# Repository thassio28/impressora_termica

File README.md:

# impressora_termica
Impressora térmica  com atmega328p e cabeça térmica LTP02-245.

Para fazer uma impressão deve ser enviado o texto por meio da porta serial com o comando CR (13) ao final da frase, ao apertar o botão o texto é impresso e é retornado pela serial o texto recebido.

Tensão comunicação 3,3V
BAUD = 9600
Tensão máxima da cabeça térmica (VP) 8V.
Clock interno 8 Mhz

Código e esquema ainda em fase de desenvolvimento.

Versão 1

Video impresão de texto: https://youtube.com/shorts/1QFV2fXhjIA?feature=share

Atualização futura, impressão de imagem: https://youtube.com/shorts/7ARQ239Vu7w?feature=share

Versão 2
Atualização futura 2, talvez display OLED.

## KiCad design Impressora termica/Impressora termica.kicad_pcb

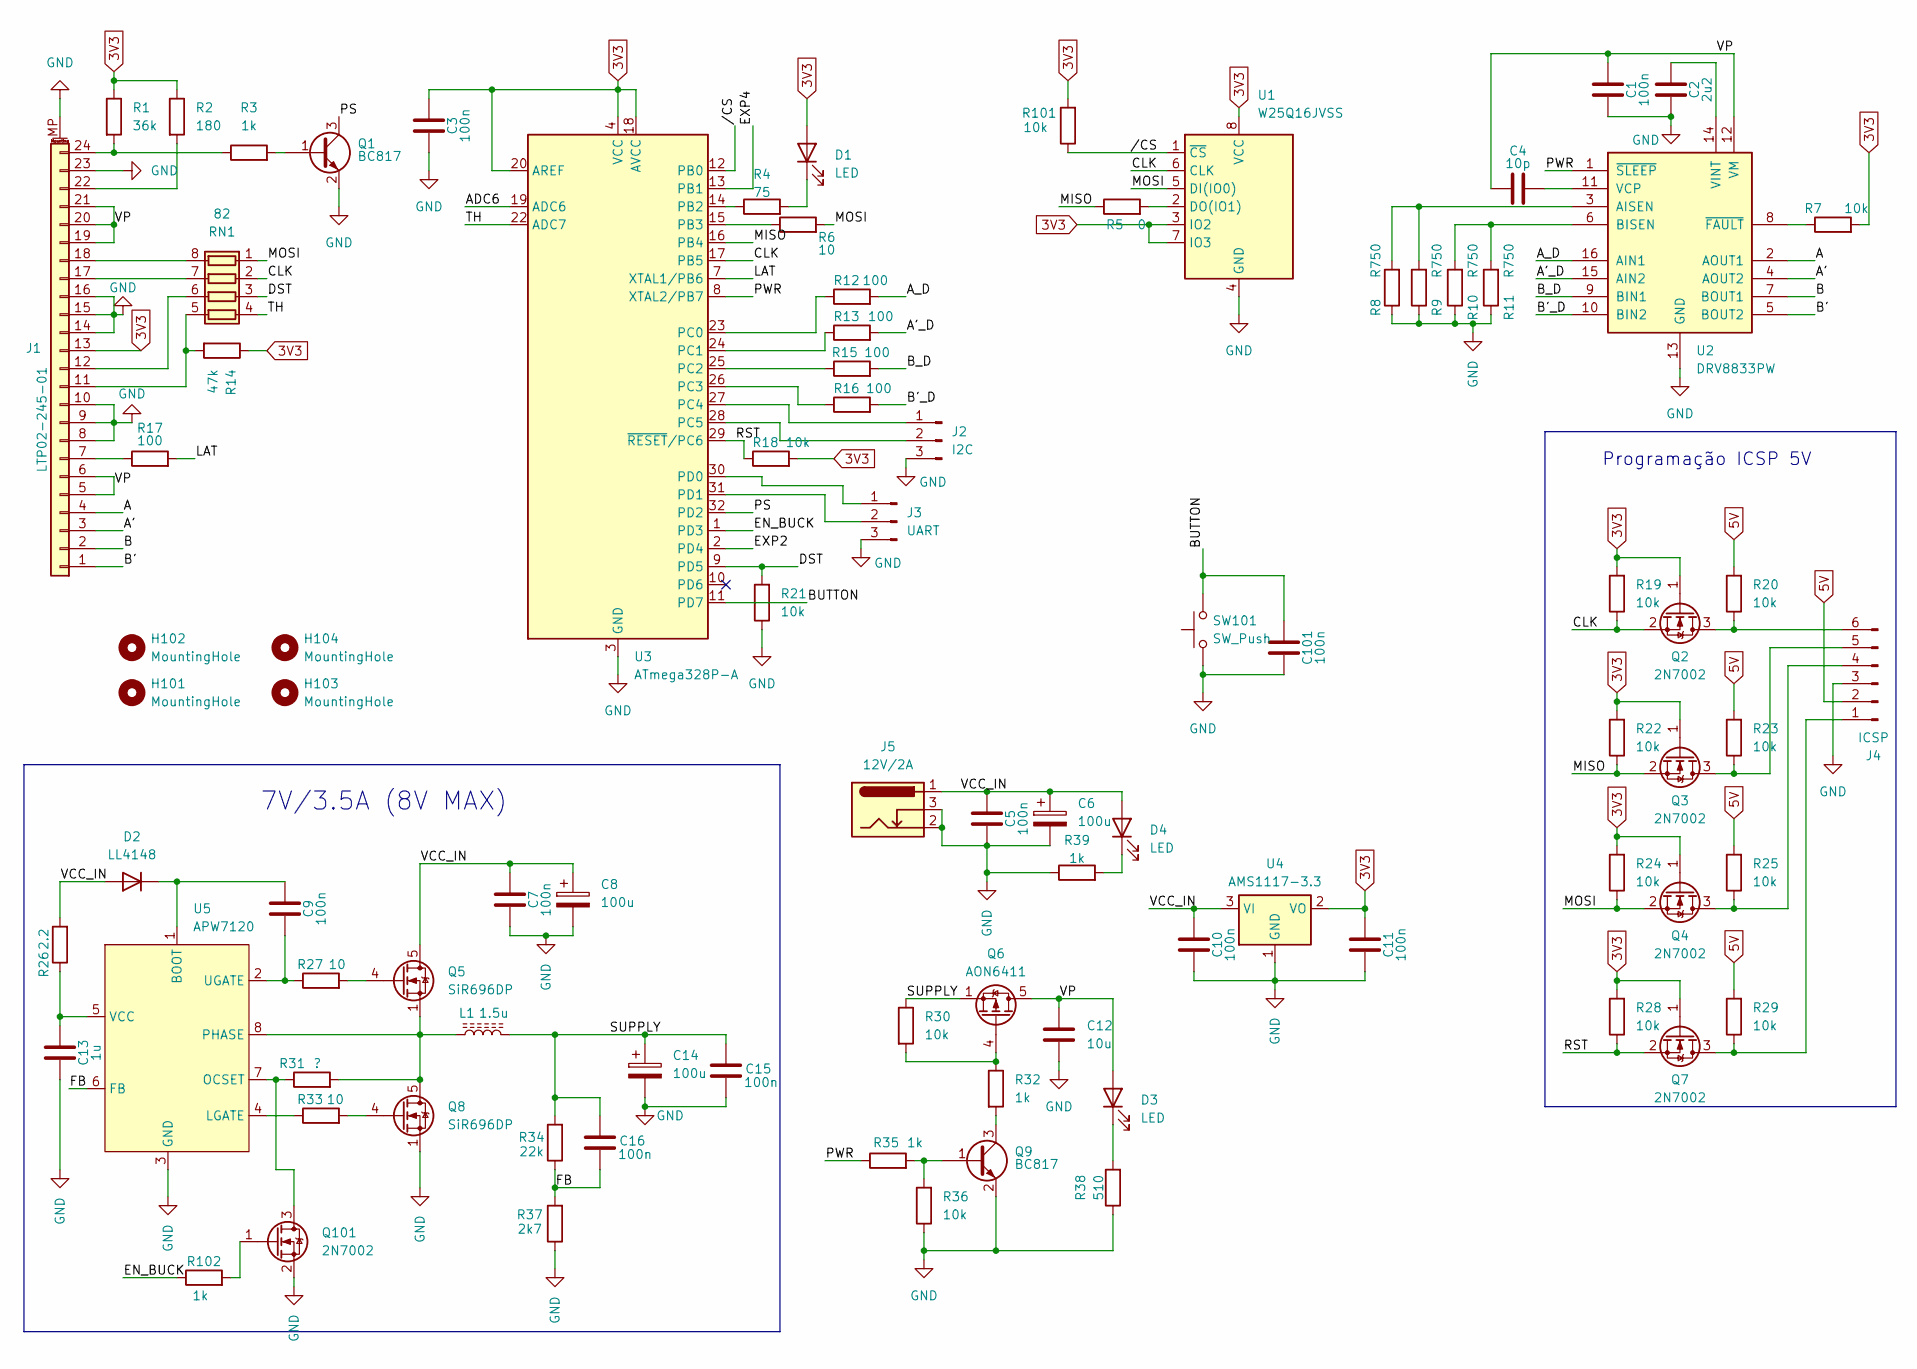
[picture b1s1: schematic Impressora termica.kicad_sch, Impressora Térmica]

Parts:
C1, C3, C5, C7, C9, C10, C11, C15, C16, C101: 100n; C_0805_2012Metric
C2: 2u2; C_0805_2012Metric
C4: 10p; C_0805_2012Metric
C6: 100u; CP_Elec_6.3x4.5
C8, C14: 100u; CP_Elec_5x4.5
C12: 10u; C_0805_2012Metric
C13: 1u; C_0805_2012Metric
D1, D3, D4: LED; LED_0805_2012Metric
D2: LL4148; D_MiniMELF
H101, H102, H103, H104: MountingHole; MountingHole_3.2mm_M3_DIN965
J1: LTP02-245-01; Hirose_FH12-24S-0.5SH_1x24-1MP_P0.50mm_Horizontal
J2: I2C; PinHeader_1x03_P2.54mm_Vertical
J3: UART; PinHeader_1x03_P2.54mm_Vertical
J4: ICSP; PinHeader_1x06_P2.54mm_Vertical
J5: 12V/2A; BarrelJack_GCT_DCJ200-10-A_Horizontal
L1: 1.5u; L_APV_ANR8040
Q1, Q9: BC817; SOT-23
Q2, Q3, Q4, Q7, Q101: 2N7002; SOT-23
Q5, Q8: SiR696DP; DFN8_3x3_EP_AOS
Q6: AON6411; DFN8_3x3_EP_AOS
R1: 36k; R_0603_1608Metric
R2: 180; R_0603_1608Metric
R3, R35: 1k; R_0805_2012Metric
R4: 75; R_0603_1608Metric
R5: 0; R_0603_1608Metric
R6: 10; R_0805_2012Metric
R7: 10k; R_1206_3216Metric
R8, R9, R10, R11: R750; R_0805_2012Metric
R12, R13, R15, R16: 100; R_0805_2012Metric
R14: 47k; R_0805_2012Metric
R17: 100; R_0603_1608Metric
R18: 10k; R_0805_2012Metric
R19, R20, R21, R22, R23, R24, R25, R28, R29, R30, R36, R101: 10k; R_0603_1608Metric
R26: 2.2; R_0805_2012Metric
R27, R33: 10; R_0603_1608Metric
R31: ?; R_0805_2012Metric
R32, R39, R102: 1k; R_0603_1608Metric
R34: 22k; R_0603_1608Metric
R37: 2k7; R_0603_1608Metric
R38: 510; R_0603_1608Metric
RN1: 82; R_Array_Convex_4x0603
SW101: SW_Push; SW_SPST_CK_RS282G05A3
U1: W25Q16JVSS; SOIC-8_5.23x5.23mm_P1.27mm
U2: DRV8833PW; TSSOP-16_4.4x5mm_P0.65mm
U3: ATmega328P-A; TQFP-32_7x7mm_P0.8mm
U4: AMS1117-3.3; SOT-223-3_TabPin2
U5: APW7120; SOP-8_5.28x5.23mm_P1.27mm

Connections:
3V3: C3.2, C11.2, D1.2 (A), J1.13, Q2.1 (G), Q3.1 (G), Q4.1 (G), Q7.1 (G), R1.1, R2.1, R7.2, R14.1, R18.2, R19.2, R22.2, R24.2, R28.2, R101.2, U1.3 (IO2), U1.7 (IO3), U1.8 (VCC), U3.4 (VCC), U3.6 (VCC), U3.18 (AVCC), U3.20 (AREF), U4.2 (VO)
5V: J4.2, R20.2, R23.2, R25.2, R29.2
/A: J1.4, U2.2 (AOUT1)
/A': J1.3, U2.4 (AOUT2)
/A'_D: R13.2, U2.15 (AIN2)
/ADC6: U3.19 (ADC6)
/A_D: R12.2, U2.16 (AIN1)
/B: J1.2, U2.7 (BOUT1)
/B': J1.1, U2.5 (BOUT2)
/B'_D: R16.2, U2.10 (BIN2)
/BUTTON: C101.2, SW101.2, U3.11 (PD7)
/B_D: R15.2, U2.9 (BIN1)
/CLK: Q2.2 (S), R19.1, RN1.2 (R2.1), U1.6 (CLK), U3.17 (PB5)
/DST: R21.2, RN1.3 (R3.1), U3.9 (PD5)
/EN_BUCK: R102.1, U3.1 (PD3)
/EXP2: U3.2 (PD4)
/EXP4: U3.13 (PB1)
/FB: C16.1, R34.1, R37.2, U5.6 (FB)
/LAT: R17.2, U3.7 (XTAL1/PB6)
/MISO: Q3.2 (S), R5.1, R22.1, U3.16 (PB4)
/MOSI: Q4.2 (S), R6.2, R24.1, RN1.1 (R1.1), U1.5 (DI(IO0))
/PS: Q1.3 (C), U3.32 (PD2)
/PWR: R35.1, U2.1 (~SLEEP), U3.8 (XTAL2/PB7)
/RST: Q7.2 (S), R18.1, R28.1, U3.29 (~RESET/PC6)
/SUPPLY: C14.1, C15.2, C16.2, L1.2, Q6.1 (S), Q6.2 (S), Q6.3 (S), R30.1, R34.2
/TH: RN1.4 (R4.1), U3.22 (ADC7)
/VCC_IN: C5.2, C6.1, C7.2, C8.1, C10.2, D2.2 (A), D4.2 (A), J5.1, Q5.5 (D), R26.2, U4.3 (VI)
/VP: C1.2, C4.1, C12.1, D3.2 (A), J1.5, J1.6, J1.19, J1.20, J1.21, Q6.5 (D), U2.12 (VM)
//CS: R101.1, U1.1 (~CS), U3.12 (PB0)
GND: C1.1, C2.1, C3.1, C5.1, C6.2, C7.1, C8.2, C10.1, C11.1, C12.2, C13.1, C14.2, C15.1, C101.1, J1.8, J1.9, J1.10, J1.14, J1.15, J1.16, J1.23, J1.MP (MountPin), J2.3, J3.3, J4.3, J5.2, J5.3, Q1.2 (E), Q8.1 (S), Q8.2 (S), Q8.3 (S), Q9.2 (E), Q101.2 (S), R8.1, R9.1, R10.1, R11.1, R21.1, R36.1, R37.1, R38.1, R39.1, SW101.1, U1.4 (GND), U2.13 (GND), U3.3 (GND), U3.5 (GND), U3.21 (GND), U4.1 (GND), U5.3 (GND)
unnamed: D1.1 (K), R4.2
unnamed: C9.2, D2.1 (K), U5.1 (BOOT)
unnamed: D3.1 (K), R38.2
unnamed: D4.1 (K), R39.2
unnamed: J1.7, R17.1
unnamed: J1.11, R14.2, RN1.5 (R4.2)
unnamed: J1.12, RN1.6 (R3.2)
unnamed: J1.17, RN1.7 (R2.2)
unnamed: J1.18, RN1.8 (R1.2)
unnamed: J1.22, R2.2
unnamed: J1.24, R1.2, R3.1
unnamed: J2.1, U3.27 (PC4)
unnamed: J2.2, U3.28 (PC5)
unnamed: J3.1, U3.30 (PD0)
unnamed: J3.2, U3.31 (PD1)
unnamed: J4.1, Q7.3 (D), R29.1
unnamed: J4.4, Q4.3 (D), R25.1
unnamed: J4.5, Q3.3 (D), R23.1
unnamed: J4.6, Q2.3 (D), R20.1
unnamed: Q1.1 (B), R3.2
unnamed: Q5.4 (G), R27.2
unnamed: Q6.4 (G), R30.2, R32.1
unnamed: L1.1, Q5.1 (S), Q5.2 (S), Q5.3 (S), Q8.5 (D), R31.2, U5.8 (PHASE)
unnamed: Q8.4 (G), R33.2
unnamed: Q9.1 (B), R35.2, R36.2
unnamed: Q9.3 (C), R32.2
unnamed: Q101.3 (D), R31.1, U5.7 (OCSET)
unnamed: Q101.1 (G), R102.2
unnamed: R5.2, U1.2 (DO(IO1))
unnamed: R8.2, R9.2, U2.3 (AISEN)
unnamed: R10.2, R11.2, U2.6 (BISEN)
unnamed: C4.2, U2.11 (VCP)
unnamed: C2.2, U2.14 (VINT)
unnamed: R7.1, U2.8 (~FAULT)
unnamed: R4.1, U3.14 (PB2)
unnamed: R6.1, U3.15 (PB3)
unnamed: R12.1, U3.23 (PC0)
unnamed: R13.1, U3.24 (PC1)
unnamed: R15.1, U3.25 (PC2)
unnamed: R16.1, U3.26 (PC3)
unnamed: R33.1, U5.4 (LGATE)
unnamed: C9.1, R27.1, U5.2 (UGATE)
unnamed: C13.2, R26.1, U5.5 (VCC)

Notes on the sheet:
7V/3.5A (8V MAX)
Programação ICSP 5V

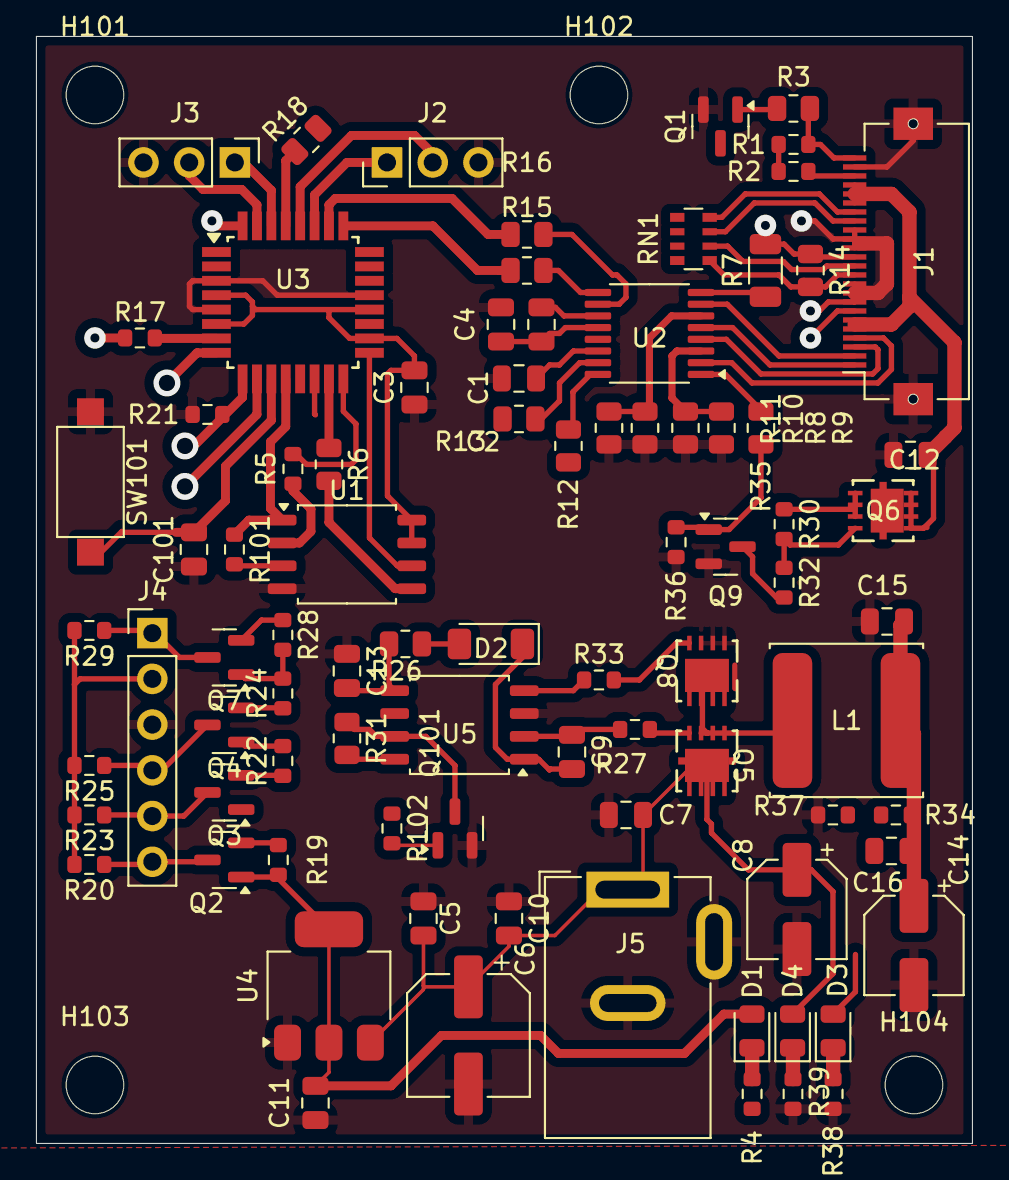
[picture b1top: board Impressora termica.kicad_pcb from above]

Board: 2 copper layers, 52.0 x 61.5 mm, 89 parts (0 on the bottom side), 70 nets.

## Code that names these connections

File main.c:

/* 
 * File:   main.c
 * Author: thassio lima
 *
 * Created on February 9, 2025, 10:07 PM
 */
#define F_CPU 8000000

#include <stdio.h>
#include <stdlib.h>
#include <avr/io.h>
#include <avr/interrupt.h>
#include <util/delay.h>
#include "font.h"
#include <string.h>


void string(void);
void print(void);
void send(void);
void USART_Transmit(void);

volatile uint8_t cont=0; //numero step
volatile uint8_t step[8]= {0b00001010,0b00000010,0b00000110,0b00000100,0b00000101,0b00000001,0b00001001,0b00001000};
volatile uint16_t i=0;    
    /*
                 0b00001000,
				 0b00001001,
				 0b00000001,
				 0b00000101,
				 0b00000100,
				 0b00000110,
				 0b00000010,
				 0b00001010};*/
 char buffer[500];// = "!Frase de teste com quebra de linha";
 char frase[100];

uint16_t tam=0; //tamanho da string
uint8_t linhas;
uint8_t li=0;
uint8_t pos=0;
uint8_t linha=0;
uint8_t lat=0; //verificar quantidade de lat

  uint16_t offset;
uint8_t L=0; //linha matriz caracter
uint8_t n_lat=0;


ISR(TIMER0_OVF_vect){
//PORTB ^=(1<<PB2);//desligar led

PORTC = step[cont];

TCCR0A ^=(1<<COM0B0) | (1<<COM0B1); //ativar desativar OCRB


//percorrer vetor do step
cont++;
n_lat++;
if(n_lat==4){ //enviar a cada 2 lat
    send();
    n_lat=0;
}
if(cont==8) //zerar vetor step
   cont=0;


  
//TCCR0B ^= 0b00000011; //desativar timer
 
 }//end timer0
 
// ISR(SPI_STC_vect){}


ISR(INT0_vect){
PORTB &=~(1<<PB7);//desligar alimentação motor/resistencia
PORTB |=(1<<PB2);//desligar led

//TCCR0B = 0; // desativar timer
TCCR0B &=~(1<<CS00);
TCCR0B &=~(1<<CS01);


}


ISR(ADC_vect){
   
    if(ADCH<25){ //temperatura maior que 75ºC
     PORTB &=~(1<<PB7);//desligar alimentação motor/resistencia
     PORTB |=(1<<PB2);//desligar led
  //   TCCR0B = 0; //desativa timer
   TCCR0B &=~(1<<CS00);
   TCCR0B &=~(1<<CS01);

    }
}

ISR(USART_RX_vect){
    
    buffer[i] = UDR0;
    
    if(buffer[i] == 13) //carriage feed
    {
       // print();
        tam = i;//memcpy(frase,frase,i);
        i=0;
   
    }
    else{
       i++;
    } 
     

}



int main() {

   


//PORTAS
    
DDRB = 0xff;
DDRC = 0b00001111;
PORTC = 0;

DDRD |=(1<<DDD6);//ocr0a /nao usar
DDRD |= (1<<DDD5);//porta resistencia
DDRD &=~(1<<DDD2); //porta sensor
DDRD &= ~(1<<DDD7);//porta botão
DDRD &=~(1<<DDD4);//teste

PORTD &=~(1<<PD6);//ocr0a /nao usar
PORTD |=(1<<PD2); //pull up sensor
PORTD &=~(1<<PD5);//desativar resitencia
PORTD |= (1<<PD7);//pull up botao
PORTB |=(1<<PB6); //porta LAT
PORTD |=(1<<PD4);//teste

//CONFIGURAR SPI
PORTB |=(1<<PB3) | (1<<PB5) |(1<<PB2);
SPCR = (1<<SPE) | (1<<DORD) |  (1<<MSTR);// | (1<<SPIE);
SPSR = (1<<SPI2X);

//CONFIGURAR UART
UBRR0 = 51;//9600
UCSR0A = 0;
UCSR0B = (1<<RXCIE0) | (1<<RXEN0) | (1<<TXEN0);
UCSR0C = (1<<UCSZ01) | (1<<UCSZ00);
//CONFIGURAR INTERRUPCAO

EICRA = 0;// level baixo (1<<ISC01); //borda de descida gera interrupcao int0
EIMSK = (1<<INT0); //pino 32

//CONFIGURAR ADC

ADMUX = (1<<REFS0) | (1<<MUX0) | (1<<MUX1) | (1<<MUX2) | (1<<ADLAR);
ADCSRA = (1<<ADEN) | (1<<ADSC) | (1<<ADATE) | (1<<ADPS0) | (1<<ADPS1) | (1<<ADPS2)| (1<<ADIE);
ADCSRB = (1<<ADTS2);//Timer/Counter0 overflow


//CONGIFURAR TIMER
TCCR0A = 0;
TCCR0B = 0;

OCR0A = 115;//frequencia ->+
OCR0B = 70;//duty
TCCR0A = (1<<COM0B0) | (1<<COM0B1) | (1<<WGM00) | (1<<WGM01); // setar pino DST pulso, modo invertido setar comparação limpar do topo
TCCR0B = (1<<CS00)| (1<<CS01) | (1<<WGM02); //clock/64

TIMSK0 = (1<<TOIE0);

TCCR0B ^= 0b00000011; //desativar timer
sei();

   
//print();
//PORTC = 0b00001010; //step inicial do motor
   
   
   
            //TCCR0B ^= 0b00000011;
//print();
   
   
  while(1){
        if(!(PIND &(1<<PD7))){
            while(!(PIND &(1<<PD7)));
                     //PORTB ^=(1<<PB2);// desliga led   
            USART_Transmit();
         print();  
         //USART_Transmit();
        }
        /*
        else if(!(PIND &(1<<PD4))){
            while(!(PIND &(1<<PD4)));
                     PORTB ^=(1<<PB2);// desliga led 
        }
        */
        
     };//end while
   return 0;
 }//end main

void string(void){

  
    linhas = (tam/24)+1;    //quantidade de linhas
    
    while(tam != linhas*24){
        buffer[tam]= ' ';    //preencher resto da frase com espaço
        tam++;
    }
    buffer[tam] = 13; //CR no ultimo caracter
    
}

void send(void){

   uint8_t data;
  
  if(buffer[pos+linha] == 13){ //desligar/parar ao chegar ao fim
      TCCR0B &=~(1<<CS00);//desligar timer
      TCCR0B &=~(1<<CS01);
      PORTB &=~(1<<PB7); //desligar power
      PORTB |=(1<<PB2);// desliga led
      pos=0, linha=0, offset=0,li=0,L=0,cont=0;//zerar variaveis, posicao inicial
      memset(buffer,13,500); //limpar buffer

  }
    while(pos <24){
        
// bytes_per_char = font_height * (font_width / 8 + ((font_width % 8) ? 1 : 0))
// offset = (ascii_code(character) - ascii_code(' ')) * bytes_per_char
// data = consolas_20pt[offset]
// 
        
        // bytes_per_char = 32*(16/8+((16%8)? 1:0));
         offset = (buffer[pos+linha] - 32) * 64;
         data = pgm_read_byte_near(&font[offset+li+L]);
         li++;//proximo byte
        // letra = pgm_read_byte_near(&font[(((frase[pos+li]-32)*64)+(byte))]); //enviar uma letra
        SPDR = data;
        while(!(SPSR & (1<<SPIF)));  //aguardar o envio
    
        data = pgm_read_byte_near(&font[offset+li+L]);

        //letra = pgm_read_byte_near(&font[(((frase[pos+li]-32)*64)+(byte+1))]); //enviar uma letra
        SPDR = data;
        while(!(SPSR & (1<<SPIF)));
        
        li=0;//zerar posicao do byte
            ++pos; //proximo caracter
           
        }
  
   pos=0;//posicao na string
   L+=2;//linha de texto
  
  
    PORTB ^=(1<<PB6); // LAT gravar dados
    PORTB ^=(1<<PB6);
    if(L>62){ //proxima linha na impressao
    linha+=24;
    L=0;
    }
    
    
}

void print(void){
    PORTB &=~(1<<PB2); //ligar led
    string();//converter frase da memoria
    send();
    PORTB |=(1<<PB7); // Power
    PORTC = 0b00001010; //step inicial do motor
    TCCR0B ^= 0b00000011; //ativar timer
    
}

void USART_Transmit(void)
{
/* Wait for empty transmit buffer */
    while(buffer[i] != 13){
        PORTB &=~(1<<PB2); //ligar led
while (!(UCSR0A & (1<<UDRE0)));
/* Put data into buffer, sends the data */
UDR0 = buffer[i];
i++;
    }
    i=0;
    PORTB |=(1<<PB2); //desligar led
}

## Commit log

2025-02-23 Primeira versão
    Arquivo fonte e .hex, esse código permite o envio de uma frase pela porta serial e ao apertar o botão o texto é impresso.
2025-02-23 Descrição geral
2025-02-23 Esquema parcial
    Esquema não completo
2025-03-01 Versão 2
    Versão 2 do esquema com conversor buck de maior potência e conversor de nível lógico para programação ICSP.
2026-01-29 Kicad files
    Placa V2 em desenvolvimento.
